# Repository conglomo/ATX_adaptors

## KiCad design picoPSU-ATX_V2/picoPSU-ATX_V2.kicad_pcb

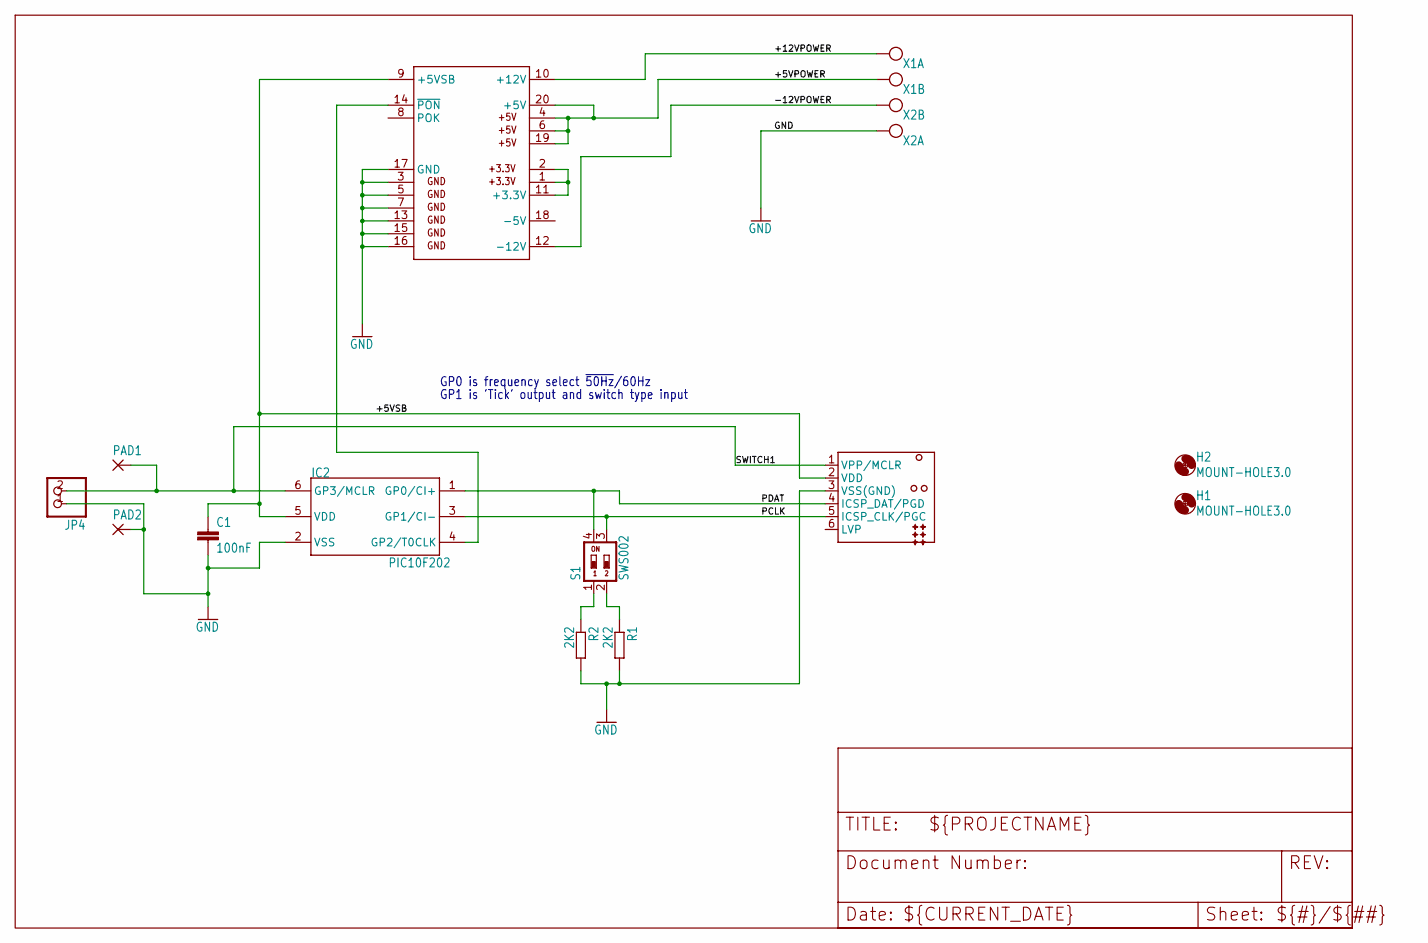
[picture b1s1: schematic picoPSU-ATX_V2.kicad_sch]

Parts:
C1: 100nF; C0805
H1, H2: MOUNT-HOLE3.0; 3,0
IC2: PIC10F202; SOT23-6
J1: TC2030-MCP-NL
JP4: PINHD-1X2; 1X02
PAD1, PAD2: 2,54/1,1; 2,54_1,1
PL1: MOLEX39-30-1200; ATX_RIGHT
R1, R2: 2K2; R0603
S1: SWS002; SMS-002
X1, X2: W237-102

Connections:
+5VPOWER: PL1.4 (+5V@1), PL1.6 (+5V@2), PL1.19 (+5V@3), PL1.20 (+5V), X1.2
+5VSB: C1.1, IC2.5 (VDD), J1.2 (VDD), PL1.9 (+5VSB)
+12VPOWER: PL1.10 (+12V), X1.1
-12VPOWER: PL1.12 (-12V), X2.2
GND: C1.2, IC2.2 (VSS), J1.3 (VSS(GND)), JP4.1, PAD2.1, PL1.3 (GND@1), PL1.5 (GND@2), PL1.7 (GND@3), PL1.13 (GND@4), PL1.15 (GND@5), PL1.16 (GND@6), PL1.17 (GND), R1.2, R2.2, X2.1
unnamed: R2.1, S1.1
unnamed: R1.1, S1.2
unnamed: PL1.1 (+3.3V@1), PL1.2 (+3.3V@2), PL1.11 (+3.3V)
PCLK: IC2.3 (GP1/CI-), J1.5 (ICSP_CLK/PGC), S1.3
PDAT: IC2.1 (GP0/CI+), J1.4 (ICSP_DAT/PGD), S1.4
PWRON: IC2.4 (GP2/T0CLK), PL1.14 (~PON)
SWITCH1: IC2.6 (GP3/MCLR), J1.1 (VPP/MCLR), JP4.2, PAD1.1

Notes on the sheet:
GP1 is 'Tick' output and switch type input
GP0 is frequency select ~{50Hz}/60Hz

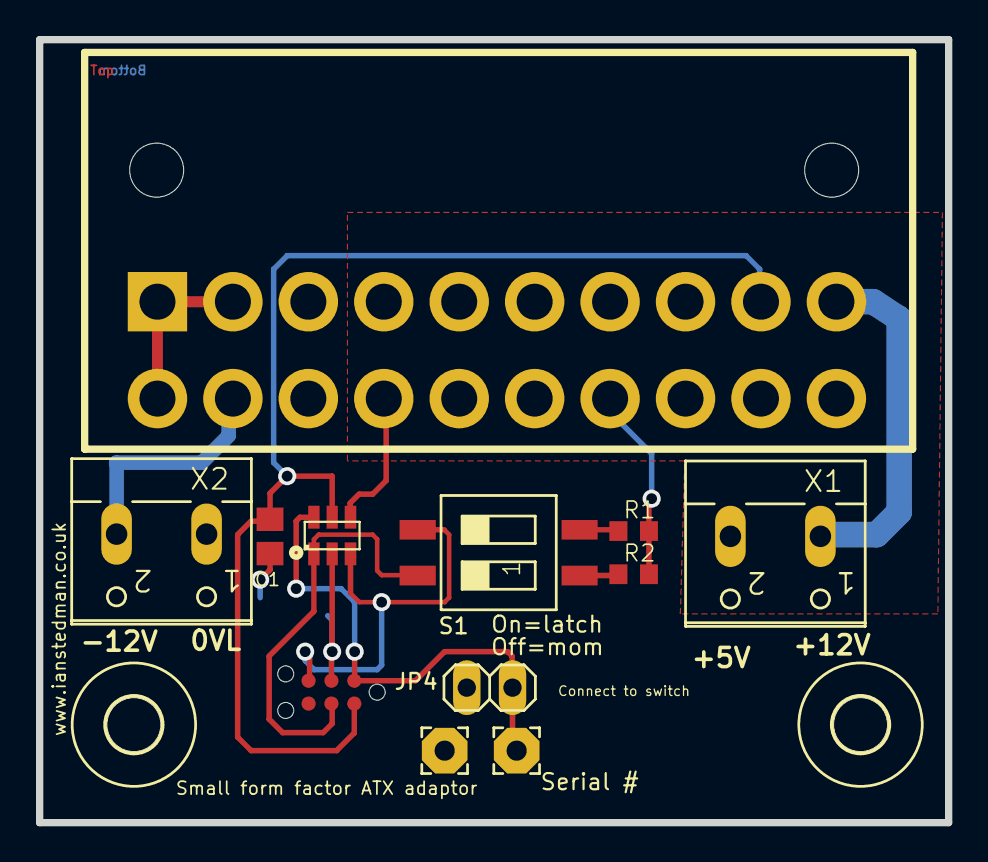
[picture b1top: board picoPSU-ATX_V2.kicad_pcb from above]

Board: 2 copper layers, 50.5 x 43.5 mm, 14 parts (0 on the bottom side), 12 nets.

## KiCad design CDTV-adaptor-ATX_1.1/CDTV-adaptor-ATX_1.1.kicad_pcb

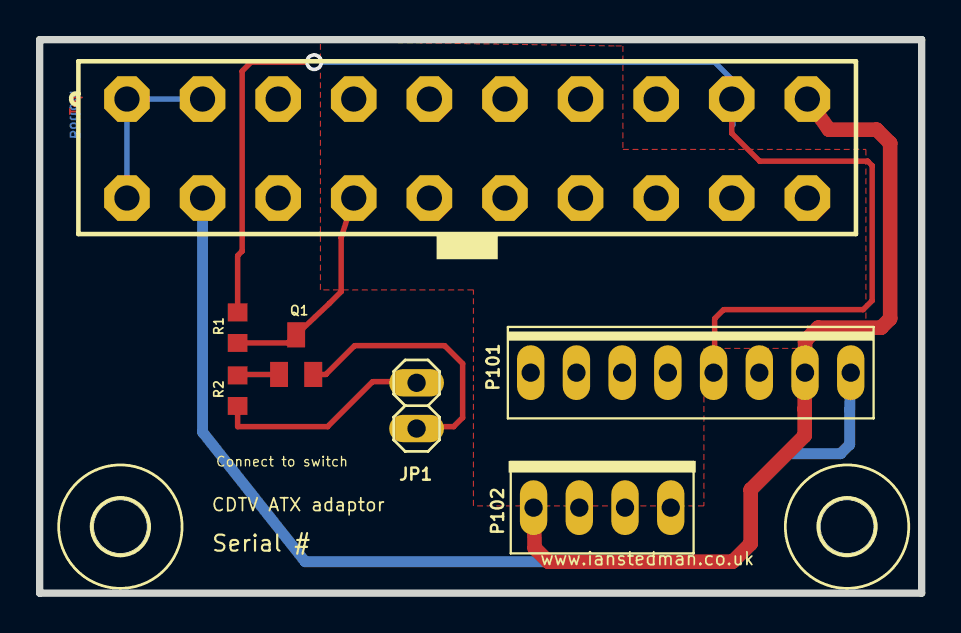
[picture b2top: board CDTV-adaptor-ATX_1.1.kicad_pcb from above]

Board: 2 copper layers, 49.0 x 30.8 mm, 9 parts (0 on the bottom side), 9 nets.

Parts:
H1, H2: MOUNT-HOLE3.0; 3,0
J2: ATXP20; MOLEX39281203
JP1: 1X02
P101: MOLEX_KK8
P102: MOLEXKK_4; MA04-1
Q1: BC846; SOT23
R1: 220R; R0603
R2: 2K2; R0603

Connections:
+5VPOWER: J2.4, J2.6, J2.19, J2.20, P101.7, P101.8, P102.1
+5VSB: J2.9, P101.4, R1.1
+12VPOWER: J2.10, P101.2, P102.4
-12VPOWER: J2.12, P101.1
GND: J2.3, J2.5, J2.7, J2.13, J2.15, J2.16, J2.17, JP1.1, P101.3, P101.5, P101.6, P102.2, P102.3, Q1.2
unnamed: Q1.1, R2.1
unnamed: J2.1, J2.2, J2.11
SWITCH: JP1.2, R2.2
~PON: J2.14, Q1.3, R1.2

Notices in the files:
parts and their libraries:
PADDescription 1MCLR/Vpp 2Vdd 3GND 4PGD (ISPDAT) 5PGC (ISPCLK) 6nc (used for LVP) ©2009 ROFA.cz - modified and updated by Robert Darlington ‹rdarlington@gmail.com›
